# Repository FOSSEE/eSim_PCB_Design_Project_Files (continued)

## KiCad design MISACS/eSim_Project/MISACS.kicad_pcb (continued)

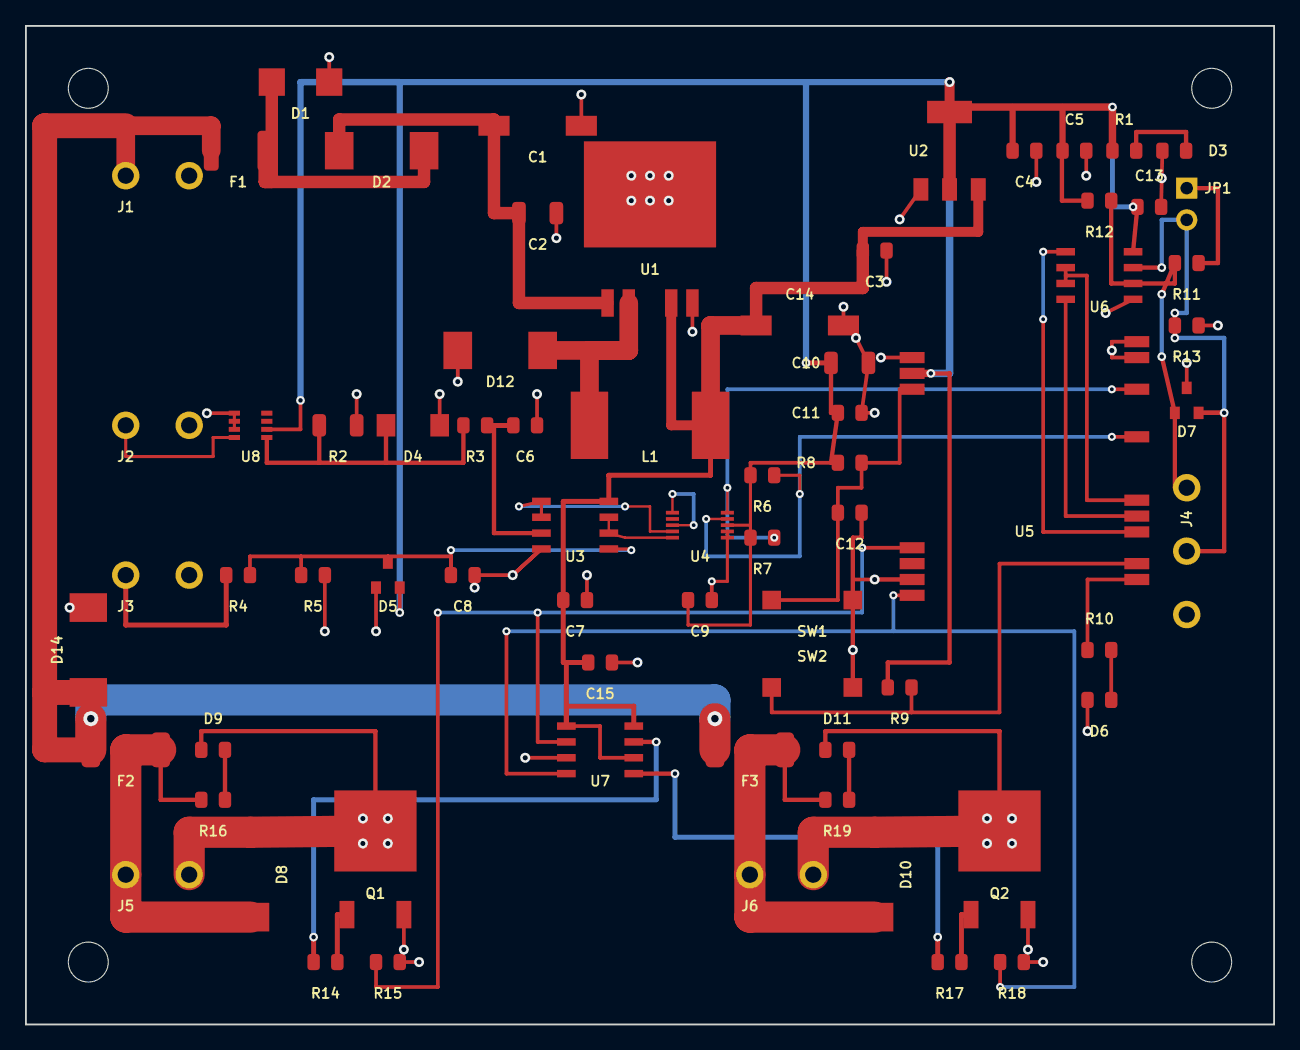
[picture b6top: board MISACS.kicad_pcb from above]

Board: 2 copper layers, 100.0 x 80.0 mm, 70 parts (0 on the bottom side), 39 nets.

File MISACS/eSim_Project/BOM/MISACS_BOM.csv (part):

Item,Qty,Reference,Value,Description,Footprint,Manufacturer,MPN
1,1,J1,PWR_IN_24V,Screw Terminal Block 2-Pin 5.08mm Pitch Horizontal 24V DC Main Power Input,"TerminalBlock_Phoenix:TerminalBlock_Phoenix_MKDS-1,5-2-5.08_1x02_P5.08mm_Horizontal",Phoenix Contact,1715721
2,1,F1,1.1A_PTC,Resettable PTC Fuse 1.1A Hold / 2.2A Trip 24V SMD 1812 (Logic Rail Protection),Fuse:Fuse_1812_4532Metric,Bourns,MF-MSMF110/33X-2
3,1,D1,SMBJ30A,"TVS Diode Unidirectional 30V 600W SMB (Power Entry Transient Voltage Suppressor, Clamps @ 48.4V)",Diode_SMD:D_SMB,Littelfuse,SMBJ30A
4,1,D2,SS36,Schottky Barrier Diode 60V 3A SMC (Logic Rail Reverse Polarity Protection),Diode_SMD:D_SMC,Vishay,SS36-E3/57T
5,1,C1,100uF_50V,Electrolytic Bulk Input Capacitor 100uF 50V Low-ESR SMD (8x10.5mm),Capacitor_SMD:CP_Elec_8x10.5,Panasonic,EEE-FK1H101P
6,1,C2,10uF_50V,Ceramic High-Frequency Bypass Capacitor 10uF 50V X7R 1206 SMD,Capacitor_SMD:C_1206_3216Metric,KEMET,C1206C106K5RAC7800
7,1,U1,LM2576HVS-5.0,Step-Down Switching Voltage Regulator 5V 3A High-Voltage TO-263-5 (LM2576HVS),Package_TO_SOT_SMD:TO-263-5_TabPin3,Texas Instruments,LM2576HVS-5.0/NOPB
8,1,D8,SS56,Schottky Barrier Diode 60V 5A SMC (Actuator Channel 1 Inductive Flyback Clamping Diode),Diode_SMD:D_SMC,Vishay,SS56-E3/57T
9,1,D10,SS56,Schottky Barrier Diode 60V 5A SMC (Actuator Channel 2 Inductive Flyback Clamping Diode),Diode_SMD:D_SMC,Vishay,SS56-E3/57T
10,1,D12,SS56,Schottky Barrier Diode 60V 5A SMC (24V-to-5V Buck Converter Fast Freewheeling Catch Diode),Diode_SMD:D_SMC,Vishay,SS56-E3/57T
11,1,D14,SS56,Schottky Barrier Diode 60V 5A SMC (J1 Main 24V Power Input Reverse-Polarity Shunt Diode),Diode_SMD:D_SMC,Vishay,SS56-E3/57T
12,1,L1,100uH_1.7A,"Shielded Power Inductor 100uH 1.7A Saturation / RMS 180 mOhm Max DCR SMD (12.5x12.5mm, Limits 5V Rail to 1.15A Worst-Case / 1.32A Nom Continuous)",Inductor_SMD:L_Bourns_SRR1260,Bourns,SRR1260-101M
13,1,C14,220uF_16V,Low-ESR Bulk Output Electrolytic Capacitor 220uF 16V SMD (8x10.5mm),Capacitor_SMD:CP_Elec_8x10.5,Panasonic,EEE-FK1C221P
14,1,C3,10uF_16V,High-Frequency Ceramic Output Filter Capacitor 10uF 16V X7R 0805 SMD,Capacitor_SMD:C_0805_2012Metric,Murata,GRM21BR71C106KE15L
15,1,U2,AMS1117-3.3,Low Dropout Linear Regulator 3.3V 1A SOT-223-3 (AMS1117-3.3),Package_TO_SOT_SMD:SOT-223-3_TabPin2,Advanced Monolithic Systems,AMS1117-3.3
16,1,C4,10uF_16V,Ceramic Bulk Decoupling Capacitor 10uF 16V X7R 0805 SMD (AMS1117-3.3 Output Bulk Bypass),Capacitor_SMD:C_0805_2012Metric,Murata,GRM21BR71C106KE15L
17,1,C10,10uF,"Ceramic Bulk Decoupling Capacitor 10uF 16V X7R 1206 SMD (ESP32 3V3 Bulk Decoupling; Plausible static stability, dynamic Wi-Fi load stability pending prototype qualification; Case A tantalum hand-solderable for bench validation)",Capacitor_SMD:C_1206_3216Metric,KEMET,C1206C106K4RACTU
18,8,"C5, C6, C7, C8, C9, C11, C13, C15",100nF,Ceramic Decoupling Capacitor 100nF 50V X7R 0805 SMD,Capacitor_SMD:C_0805_2012Metric,KEMET,C0805C104K5RACTU
19,1,C12,100nF,Ceramic Timing Capacitor 100nF 50V X7R 0805 SMD (ESP32 MCU_EN RC Reset Delay Network),Capacitor_SMD:C_0805_2012Metric,KEMET,C0805C104K5RACTU
20,2,"R1, R3",1k,Thick Film Resistor 1k 1% 0.125W 0805 SMD (Power LED & RC Filter),Resistor_SMD:R_0805_2012Metric,Yageo,RC0805FR-071KL
21,1,D3,GREEN,SMD Indicator LED Green 0805 Clear (+3.3V Power Good Indicator),LED_SMD:LED_0805_2012Metric,Lite-On,LTST-C170KGKT
22,1,J2,4-20mA_IN,Screw Terminal Block 2-Pin 5.08mm Pitch Horizontal 4-20mA Loop Input,"TerminalBlock_Phoenix:TerminalBlock_Phoenix_MKDS-1,5-2-5.08_1x02_P5.08mm_Horizontal",Phoenix Contact,1715721
23,1,U8,TPS26610DDF,Active Current Limiter & Reverse Protection eFuse SOT-23-8 (TPS26610DDF),Package_TO_SOT_SMD:SOT-23-8,Texas Instruments,TPS26610DDFR
24,1,R2,100R_0.1%,Metal Film Precision Current Shunt Resistor 100 Ohm 0.1% 0.25W 25ppm 1206 SMD,Resistor_SMD:R_1206_3216Metric,Susumu,RR1220P-101-D
25,1,D4,SMAJ3.3A,TVS Diode Unidirectional 3.3V 400W SMA (4-20mA Shunt Overvoltage Clamping),Diode_SMD:D_SMA,Littelfuse,SMAJ3.3A
26,1,J3,0-10V_IN,Screw Terminal Block 2-Pin 5.08mm Pitch Horizontal 0-10V Sensor Input,"TerminalBlock_Phoenix:TerminalBlock_Phoenix_MKDS-1,5-2-5.08_1x02_P5.08mm_Horizontal",Phoenix Contact,1715721
27,1,R4,30k_0.1%,Thin Film Precision Resistor 30k 0.1% 0.125W 25ppm 0805 SMD (4:1 Voltage Divider High Side),Resistor_SMD:R_0805_2012Metric,Panasonic,ERA-6AEB303V
28,1,R5,10k_0.1%,Thin Film Precision Resistor 10k 0.1% 0.125W 25ppm 0805 SMD (4:1 Voltage Divider Low Side),Resistor_SMD:R_0805_2012Metric,Panasonic,ERA-6AEB103V
29,1,D5,BAT54S,Dual Schottky Barrier Diode Series Pair SOT-23 (Analog Input Clamping to GND/+3.3V),Package_TO_SOT_SMD:SOT-23,Diodes Inc.,BAT54S-7-F
30,1,U3,LMV358,Dual Rail-to-Rail Output Operational Amplifier SOIC-8 (LMV358),Package_SO:SOIC-8_3.9x4.9mm_P1.27mm,Texas Instruments,LMV358IDR
31,1,U4,ADS1115,Ultra-Small 16-Bit Precision Delta-Sigma ADC with PGA and I2C MSOP-10 (ADS1115),Package_SO:MSOP-10_3x3mm_P0.5mm,Texas Instruments,ADS1115IDGSR
32,2,"R6, R7",4.7k,Thick Film Resistor 4.7k 1% 0.125W 0805 SMD (I2C Bus Pull-Ups),Resistor_SMD:R_0805_2012Metric,Yageo,RC0805FR-074K7L
33,1,U5,ESP32-WROOM-32,"Wi-Fi & Bluetooth MCU Module ESP32-WROOM-32 (16MB Flash, On-Board Antenna)",RF_Module:ESP32-WROOM-32,Espressif Systems,ESP32-WROOM-32E-N16
34,2,"SW1, SW2",PTS645,Tactile Pushbutton Switch SPST-NO SMD 6x6mm (Reset and Boot Switches),Button_Switch_SMD:SW_SPST_PTS645,C&K Components,PTS645SM43SMTR92LFS
35,4,"R8, R9, R15, R18",10k,Thick Film Resistor 10k 1% 0.125W 0805 SMD (MCU Pull-Ups & Gate Pull-Downs),Resistor_SMD:R_0805_2012Metric,Yageo,RC0805FR-0710KL
36,1,D6,BLUE,SMD Indicator LED Blue 0805 Clear (MCU Heartbeat / Status Indicator),LED_SMD:LED_0805_2012Metric,Lite-On,LTST-C170TBKT
37,1,R10,1k,Thick Film Resistor 1k 1% 0.125W 0805 SMD (MCU Status LED Resistor),Resistor_SMD:R_0805_2012Metric,Yageo,RC0805FR-071KL
38,1,U6,MAX3485EESA,3.3V RS-485/RS-422 Transceiver Half-Duplex SOIC-8 Non-Isolated (MAX3485EESA+),Package_SO:SOIC-8_3.9x4.9mm_P1.27mm,Analog Devices / Maxim,MAX3485EESA+
39,1,R11,120R_1%,Thick Film Resistor 120 Ohm 1% 0.125W 0805 SMD (RS-485 Differential Bus Termination),Resistor_SMD:R_0805_2012Metric,Yageo,RC0805FR-07120RL
40,1,JP1,TERM_ENABLE,Pin Header 1x2 2.54mm Pitch Vertical with Jumper (RS-485 120 Ohm Bus Termination Enable),Connector_PinHeader_2.54mm:PinHeader_1x02_P2.54mm_Vertical,Wurth Elektronik,61300211121
41,2,"R12, R13",390R_0.1%,"Thin Film Resistor 390 Ohm 0.1% 0.125W 25ppm 0805 SMD (RS-485 Dual-Termination Fail-Safe Biasing, Yields +235.7mV Differential Idle Across 60 Ohm Terminated Bus)",Resistor_SMD:R_0805_2012Metric,Yageo,RC0805FR-07390RL
42,1,D7,SM712,Asymmetrical Bidirectional TVS Diode for Extended RS-485 Common Mode (+12V/-7V) SOT-23,Package_TO_SOT_SMD:SOT-23,Littelfuse,SM712-02HTG
43,1,J4,RS485_BUS,"Screw Terminal Block 3-Pin 5.08mm Pitch Horizontal (RS-485 Differential Bus A, B, GND)","TerminalBlock_Phoenix:TerminalBlock_Phoenix_MKDS-1,5-3-5.08_1x03_P5.08mm_Horizontal",Phoenix Contact,1715734
44,1,U7,UCC27524D,Dual 5A High-Speed Low-Side Power MOSFET Gate Driver SOIC-8 (UCC27524D),Package_SO:SOIC-8_3.9x4.9mm_P1.27mm,Texas Instruments,UCC27524D
45,2,"F2, F3",5A_FAST_FUSE,Fast-Acting Surface Mount Fuse 5.0A 125V SMD 2410 (Actuator Rail Protection),Fuse:Fuse_2410_6125Metric,Littelfuse,0451005.MRL
46,2,"R14, R17",10R,Thick Film Resistor 10 Ohm 1% 0.125W 0805 SMD (MOSFET Gate Dampening Resistor),Resistor_SMD:R_0805_2012Metric,Yageo,RC0805FR-0710RL
47,2,"Q1, Q2",IPD50N06S4L-08,N-Channel Power MOSFET 60V 50A 8.4mOhm DPAK / TO-252 (IPD50N06S4L-08),Package_TO_SOT_SMD:TO-252-2,Infineon Technologies,IPD50N06S4L-08
48,2,"D9, D11",YELLOW,SMD Indicator LED Yellow 0805 Clear (Actuator Channel Output Active Indicator),LED_SMD:LED_0805_2012Metric,Lite-On,LTST-C170KSKT
49,2,"R16, R19",2.2k,Thick Film Resistor 2.2k 1% 0.125W 0805 (Actuator LED Current Limiter),Resistor_SMD:R_0805_2012Metric,Yageo,RC0805FR-072K2L
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
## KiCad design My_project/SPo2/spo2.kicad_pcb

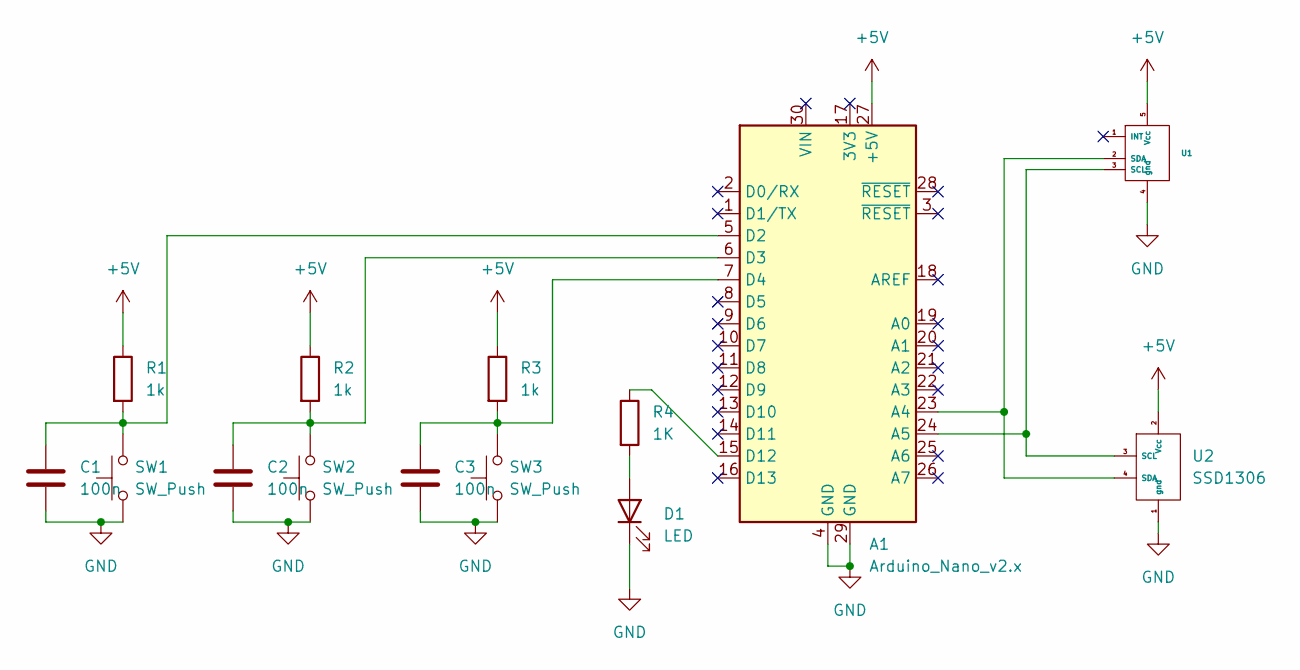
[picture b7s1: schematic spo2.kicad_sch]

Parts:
A1: Arduino_Nano_v2.x; Arduino_Nano
C1, C2, C3: 100n; C_Disc_D4.7mm_W2.5mm_P5.00mm
D1: LED; LED_D5.0mm
R1, R2, R3: 1k; R_Axial_DIN0204_L3.6mm_D1.6mm_P7.62mm_Horizontal
R4: 1K; R_Axial_DIN0204_L3.6mm_D1.6mm_P7.62mm_Horizontal
SW1, SW2, SW3: SW_Push; SW_PUSH_6mm
U1: MAX30102
U2: SSD1306

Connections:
+5V: A1.27 (+5V), R1.1, R2.1, R3.1, U1.5 (Vcc), U2.2 (Vcc)
GND: A1.4 (GND), A1.29 (GND), C1.2, C2.2, C3.2, D1.1 (K), SW1.2, SW2.2, SW3.2, U1.4 (gnd), U2.1 (gnd)
unnamed: A1.23 (A4), U1.2 (SDA), U2.4 (SDA)
unnamed: A1.24 (A5), U1.3 (SCL), U2.3 (SCL)
unnamed: A1.5 (D2), C1.1, R1.2, SW1.1
unnamed: A1.6 (D3), C2.1, R2.2, SW2.1
unnamed: A1.7 (D4), C3.1, R3.2, SW3.1
unnamed: A1.15 (D12), R4.1
unnamed: D1.2 (A), R4.2

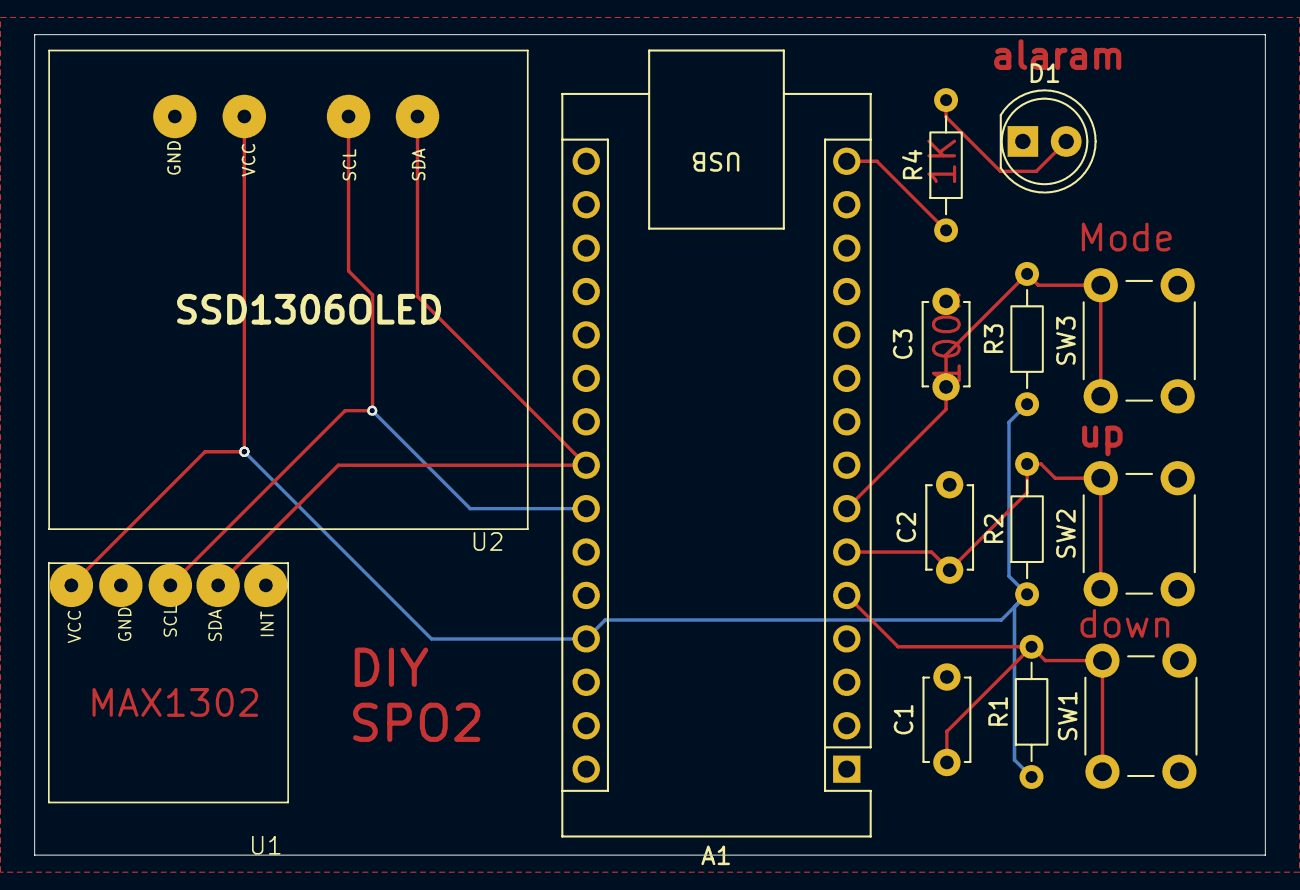
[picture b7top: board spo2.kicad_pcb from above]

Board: 2 copper layers, 72.0 x 48.0 mm, 14 parts (0 on the bottom side), 9 nets.

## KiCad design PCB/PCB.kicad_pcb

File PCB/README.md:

<div align="center">

# ⚡ ESP32 Relay & Li-ion Charger Controller

**A compact ESP32-based board that monitors a Li-ion cell, charges it with a TP4056, and switches the charger supply through a relay.**

</div>

---

## 📖 Overview

This project is a compact PCB designed in **eSim 2.5 (KiCad 6.0.11)** around an **ESP-WROOM-32**. The board:

- 🌡️ measures Li-ion cell **temperature** using an NTC thermistor,
- 🔋 measures **battery voltage** through a resistor divider,
- 🔌 **charges** a single 18650 cell using a **TP4056**,
- 🔁 uses a **5 V relay** to switch the charger's supply path, driven from the ESP32.

---

## ✨ Features

| | Feature | Ref |
|---|---|---|
| 🧠 | ESP-WROOM-32 microcontroller module | `U1` |
| 🔋 | TP4056 single-cell Li-ion charger | `U3` |
| 🪫 | Keystone 1042 holder for one 18650 cell | `BT1` |
| 🔁 | 5 V relay (G5V-1-DC5) driven by a transistor from pin **D4** | `K1`, `Q1` |
| 🛡️ | 1N4007 flyback diode across the relay coil | `D1` |
| 🌡️ | NTC thermistor + 10 kΩ resistor, read on **D36** | `RT1`, `R1` |
| 📏 | Battery voltage divider (2 × 10 kΩ), read on **D34** | `R2`, `R3` |
| ⚙️ | LM1117-3.3 regulator for the 3.3 V rail | `U2` |
| 🔩 | 2-pin screw terminal for the +5 V input | `J1` |

---

## 🧩 System Block Diagram

```mermaid
flowchart LR
    IN["+5 V Input<br/>(J1)"] --> REG["LM1117-3.3<br/>(U2)"]
    REG --> MCU["ESP-WROOM-32<br/>(U1)"]
    IN --> RLY["Relay K1"]
    MCU -- "D4" --> Q["Q1 driver"] --> RLY
    RLY --> CHG["TP4056<br/>(U3)"] --> CELL["18650 Cell<br/>(BT1)"]
    CELL --> DIV["Divider R2/R3"] -- "D34" --> MCU
    NTC["NTC RT1 + R1"] -- "D36" --> MCU
```

---

## 📌 ESP32 Pin Map

| Pin | Direction | Function |
|:---:|:---:|---|
| **D4** | Output | Relay driver (via Q1) |
| **D34** | Input (ADC) | Battery voltage (R2/R3 divider) |
| **D36** | Input (ADC) | Thermistor temperature (RT1 + R1) |

---

## 📊 Design Results

| Item | Result |
|---|:---:|
| ERC | ✅ 0 errors, 0 warnings |
| DRC | ✅ 0 violations, 0 unconnected items |
| Pads / Vias / Track segments / Nets | 78 / 27 / 118 / 47 |
| Unrouted nets | 0 |
| Copper layers defined | Front, In1.Cu, In2.Cu, Back |

---

## 🖼️ Gallery

| Schematic | PCB Layout |
|:---:|:---:|
|  |  |

| DRC (0 violations) | 3D View (angled) |
|:---:|:---:|
|  |  |

---

## 🧾 Bill of Materials

| Ref | Part | Footprint |
|---|---|---|
| BT1 | 18650 holder | `Battery:BatteryHolder_Keystone_1042_1x18650` |
| D1 | 1N4007 | `Diode_SMD:D_SMA` |
| J1 | Screw terminal 1x02 | `TerminalBlock_Phoenix_MKDS-1,5-2-5.08_1x02_P5.08mm_Horizontal` |
| K1 | G5V-1-DC5 | `G5V-1:RELAY_G5V-1-DC5` |
| Q1 | BC857 | `Package_TO_SOT_SMD:SOT-23` |
| R1, R2, R3 | 10K | `Resistor_SMD:R_0805_2012Metric` |
| RT1 | NCU15WF104D60RC | `NCU15WF104D60RC:THRMC1005X55N` |
| U1 | ESP-WROOM-32 | `ESP-WROOM-32:MODULE_ESP-WROOM-32` |
| U2 | LM1117-3.3 | `Package_TO_SOT_SMD:SOT-223-3_TabPin2` |
| U3 | TP4056 | `TP4056:SOP127P600X175-9N` |

---

## 🚀 How to Open

1. Install **eSim 2.5** (includes KiCad 6.0.11).
2. Open the project in KiCad from eSim.
3. Open the **Schematic Editor** for the circuit and the **PCB Editor** for the layout.
4. Reproduce the checks:
   - Schematic: `Inspect > Electrical Rules Checker`
   - PCB: `Inspect > Design Rules Checker`
5. Inspect the board in 3D: `View > 3D Viewer`.

---

## 🛠️ Known Notes / Possible Improvements

- [ ] **Q1 polarity:** BC857 is a PNP wired as a low-side switch with its emitter to GND. Verify this; an NPN (e.g. BC847) or an N-channel MOSFET is the usual choice.
- [ ] Add a **base resistor** between D4 and Q1.
- [ ] The TP4056 **PROG pin** needs a resistor to set the charge current.
- [ ] Add **decoupling capacitors** on the LM1117 and ESP32 supply, and an **EN pull-up** for the ESP32.
- [ ] Add an **input fuse** and **reverse-polarity protection**.

---

## 📚 Documentation

See the accompanying **design report** for the schematic, footprint assignment, PCB layout, routing methodology, DRC results and 3D views.

---

## 👤 Author

**Irfan** — Electronics Engineering (VLSI Design & Technology)

<div align="center">

⭐ If you find this project useful, consider giving it a star!

</div>

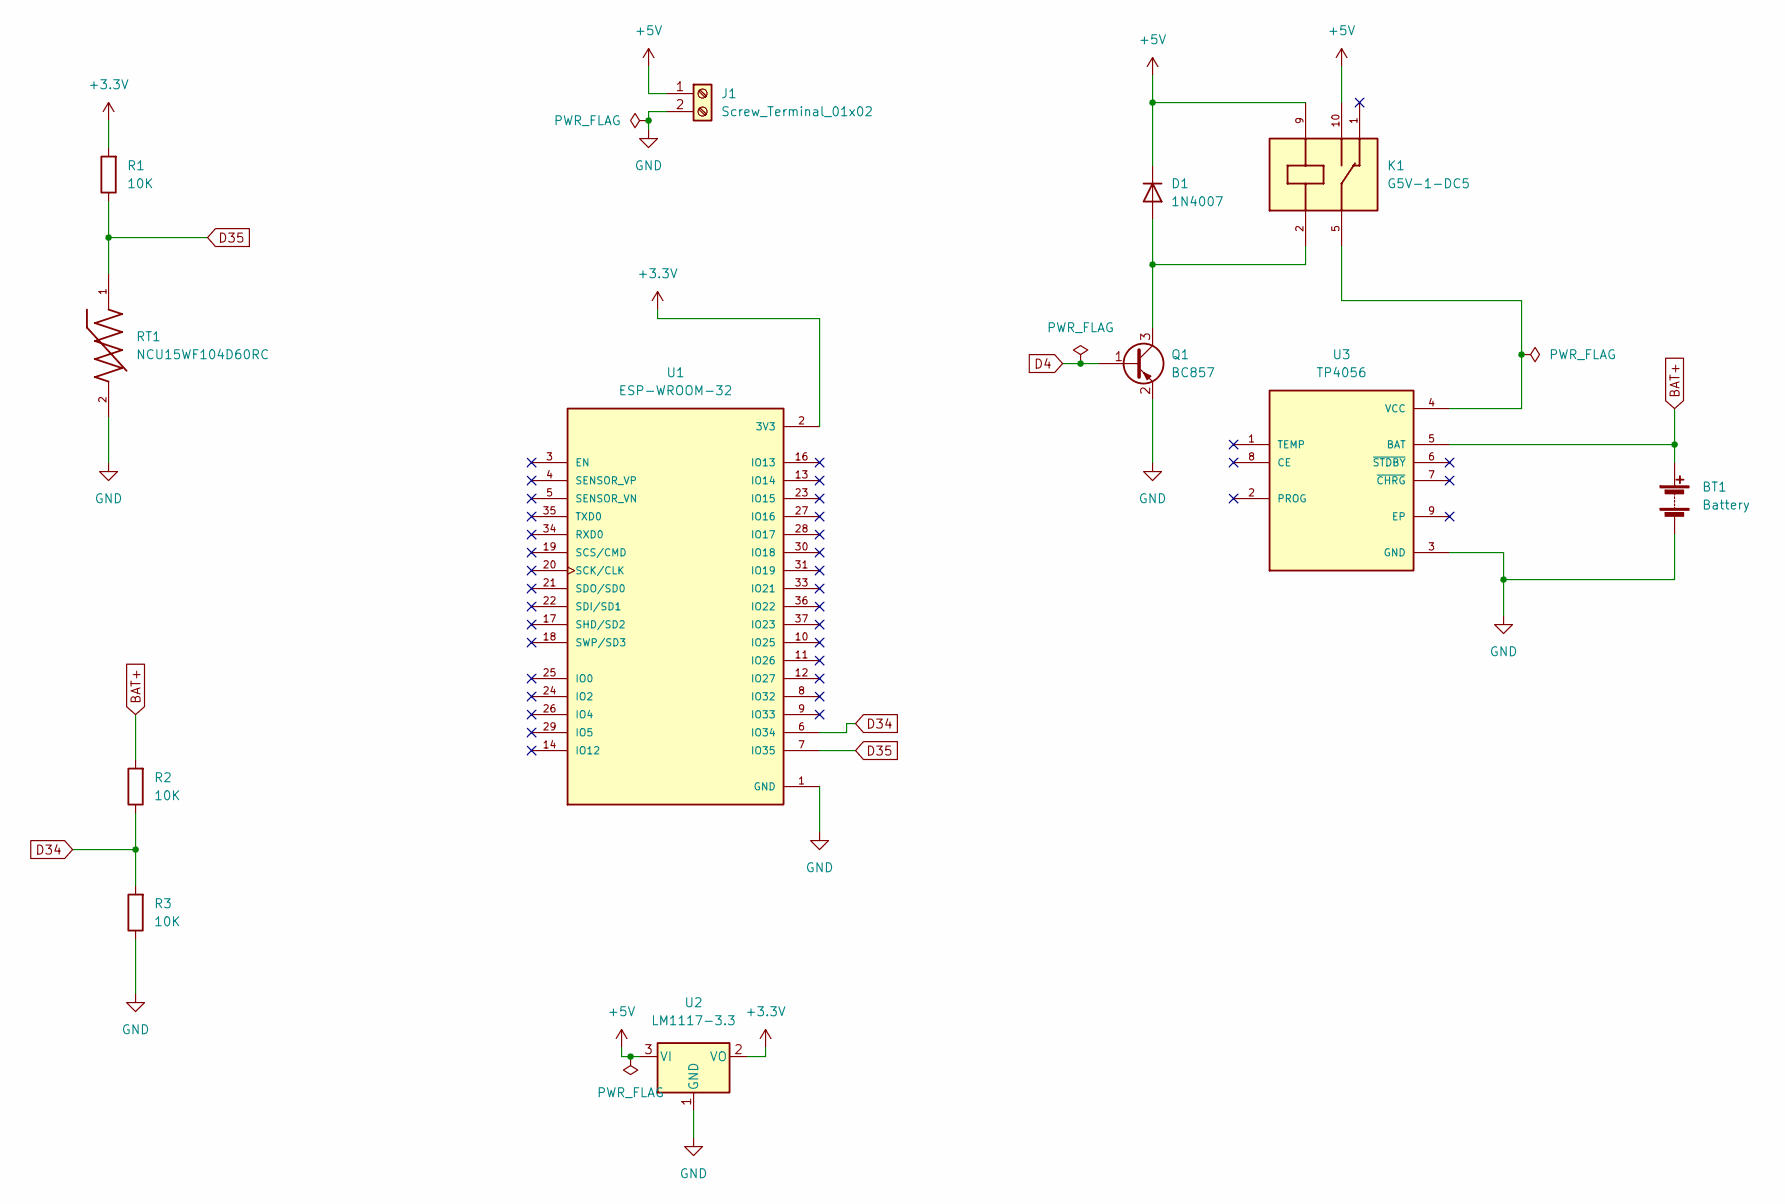
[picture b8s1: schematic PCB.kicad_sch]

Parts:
BT1: Battery; BatteryHolder_Keystone_1042_1x18650
D1: 1N4007; D_SMA
J1: Screw_Terminal_01x02; TerminalBlock_Phoenix_MKDS-1,5-2-5.08_1x02_P5.08mm_Horizont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
K1: G5V-1-DC5; RELAY_G5V-1-DC5; MPN G5V-1-DC5
Q1: BC857; SOT-23
R1, R2, R3: 10K; R_0805_2012Metric
RT1: NCU15WF104D60RC; THRMC1005X55N; MPN NCU15WF104D60RC
U1: ESP-WROOM-32; MODULE_ESP-WROOM-32; MPN ESP-WROOM-32
U2: LM1117-3.3; SOT-223-3_TabPin2
U3: TP4056; SOP127P600X175-9N; MPN TP4056

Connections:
+3.3V: R1.2, U1.2 (3V3), U2.2 (VO)
+5V: D1.1 (K), J1.1, K1.9, K1.10, U2.3 (VI)
BAT+: BT1.1 (+), R2.2, U3.5 (BAT)
BAT-: BT1.2 (-), J1.2, Q1.2 (E), R3.1, RT1.2, U1.1 (GND), U1.1.1 (GND), U1.15 (GND), U1.38 (GND), U2.1 (GND), U3.3 (GND)
D4: Q1.1 (B)
D34: R2.1, R3.2, U1.6 (IO34)
D35: R1.1, RT1.1, U1.7 (IO35)
unnamed: D1.2 (A), K1.2, Q1.3 (C)
unnamed: K1.5, K1.6, U3.4 (VCC)

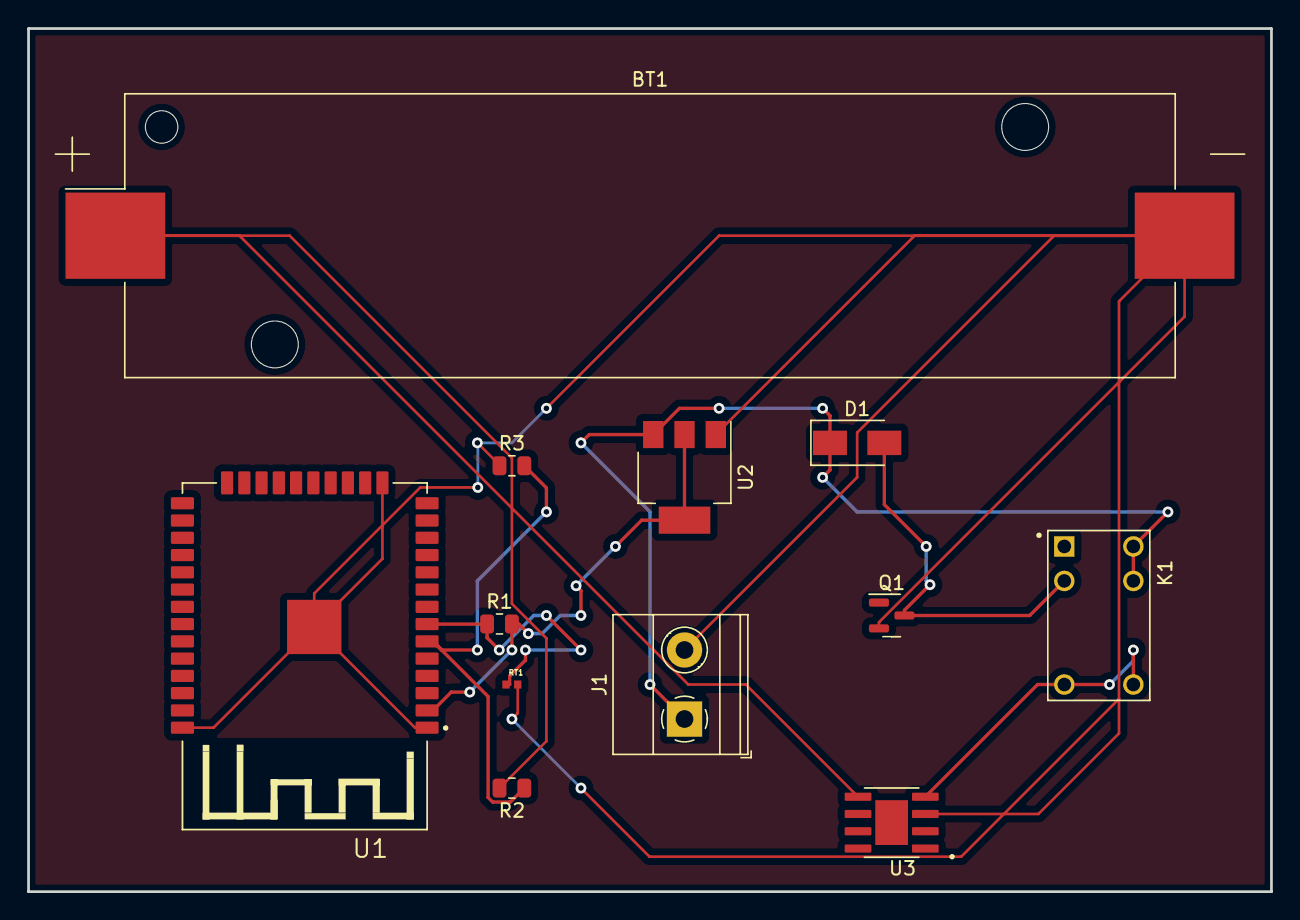
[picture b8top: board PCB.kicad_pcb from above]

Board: 4 copper layers, 91.4 x 63.5 mm, 12 parts (0 on the bottom side), 8 nets.
